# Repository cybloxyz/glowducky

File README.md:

# 🐥 GLOWDUCKY! ver.1 💡
so this glow glow ducky is a bedlamp, not really..it could be another useful things, for study lamp or when lights out or another cute lamp! 
i made this bedlamp for my little sister as gift for her achievement in school! she got first place **🐥** and she likes a little yellow duck! 
*this is my first time working with hardware things!* so i try to make the simplest project, **Lamp ⚡️**.

even in this simplest project i still got so many errors in designing schema..but yeah, trial and error!
i plan to improve this **glowducky** as soon as i learn about Attiny or Atmel, yeaa and i currently learning about Arduino.

wait i'll attach some pics!
## sailor ducky case 🐥

so this duck is going to be the case! you need to separate each body parts so you could put the lamp inside! and i plan to use 3d printer for it with white filament, 2 layers and 0% infill

## pcb and schematic design

this is the glowduck PCB! and i'll attach the schema

### Bill of Materials for each glowducky (BOM)
| Component | Specification | Qty for each lamp | Qty buy | Price | Total Price | 
| :--- | :--- | :--- | :--- | :--- | :--- |
| LED | [5mm Warm White Strawhat ](https://shopee.co.id/LED-Warm-White-5mm-Straw-Hat-Clear-Diode-Super-Bright-Round-Through-i.2178321.42170662136?xptdk=b816d7c5-0220-4b61-b76c-9c2c57219d83) | 2 | 10 | Rp.800 | Rp.8000 |
| Resistor | [330 Ohm](https://shopee.co.id/10X-RESISTOR-330-OHM-1-4W-1-METAL-FILM-i.1078675148.22483412804?xptdk=1b5f20fc-b740-4827-acae-979e2000c763) | 1 | 5 | Rp.700 | Rp.3500 |
| Switch | [8mmx8mm Latching Push Button](https://shopee.co.id/BLUE-CAP-SQUARE-PUSH-BUTTON-8X8MM-SELF-LOCKING-LATCHING-SWITCH-i.1078675148.17199189956?xptdk=031379d1-bf77-44f0-a31d-17c58174d32c) | 1 | 5 | Rp.1033 | Rp.5165 |
| Battery | CR2032 | 2 | 1 strip(5pcs) or 2 strip? | Rp.21500 | Rp.21500 |
| Battery Case | [2x CR2032 Holder](https://shopee.co.id/Baterai-Holder-2X-CR2032-6V-Battery-Case-Tempat-Baterai-Saklar-ON-OFF-i.2178321.24317995442?xptdk=1cde20a7-d5c7-4ba1-88d6-16cacaf16a91) | 1 | 5 | Rp.3600 | Rp.18000 |
| Wire | [AWG 26](https://shopee.co.id/Kabel-AWG-26-awg26-Serabut-Tembaga-Putih-Eceran-1Meter-Jumper-Cable-i.2178321.7345265115?xptdk=d2c1ef28-a399-42a3-8674-fd6ee5da9c35) | 1 (in meter) | 1 | Rp.1800 | Rp.1800 |
| Wire | [Jumper cable male-female](https://shopee.co.id/40PCS-JUMPER-CABLE-KABEL-10CM-MALE-TO-FEMALE-DUPONT-FOR-BREADBOARD-i.1078675148.23482811318?extraParams=%7B%22display_model_id%22%3A89453627299%2C%22model_selection_logic%22%3A2%7D&sp_atk=d1c997f7-9c6e-47e8-9971-6b24501d0b91&xptdk=d1c997f7-9c6e-47e8-9971-6b24501d0b91) | 3 | 1 strip(40pcs) | Rp.9500 | Rp.9500 |
| PCB | [Double layer pcb](https://shopee.co.id/Layanan-Cetak-Pcb-Single-Layer-Dan-Double-Layer-i.100172996.43623177280?xptdk=e2854418-3a2e-4cdc-aff0-7e93d7e86390) | 1 | 5 | Rp.1000 | Rp.5000 |
| Total | Rp.72465 |
| Total + shipping cost | Rp.129465 |

*nb: Price is in IDR, This design is made for minimum quantity (eg: 5 pcs PCB) and some components are not on the pcb (latching button and battery)*

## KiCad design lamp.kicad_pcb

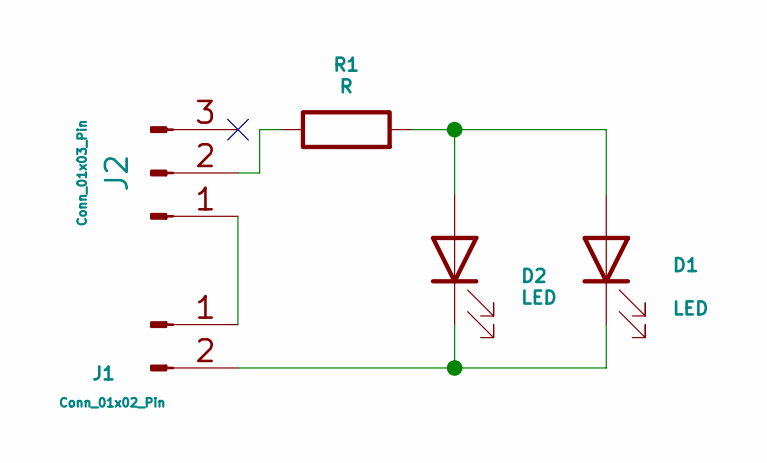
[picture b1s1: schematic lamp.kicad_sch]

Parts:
D1, D2: LED; LED_D5.0mm
J1: Conn_01x02_Pin; PinHeader_1x02_P2.54mm_Vertical
J2: Conn_01x03_Pin; PinHeader_1x03_P2.54mm_Vertical
R1: R; R_Axial_DIN0309_L9.0mm_D3.2mm_P12.70mm_Horizontal

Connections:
unnamed: D1.2 (A), D2.2 (A), R1.2
unnamed: D1.1 (K), D2.1 (K), J1.2
unnamed: J1.1, J2.1
unnamed: J2.2, R1.1

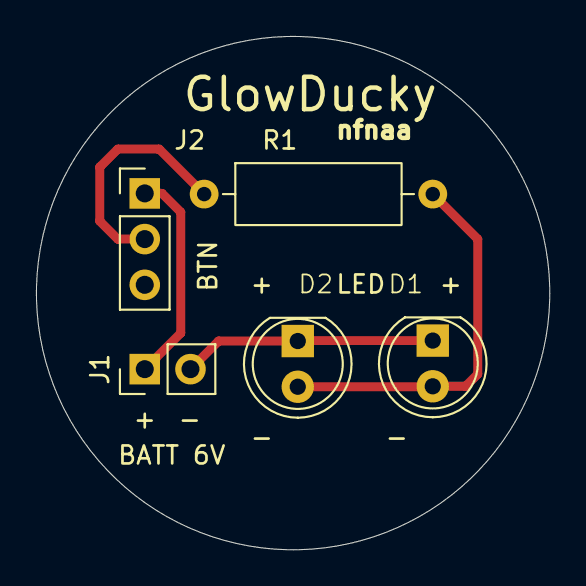
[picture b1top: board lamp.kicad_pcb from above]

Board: 2 copper layers, 28.5 x 28.5 mm, 5 parts (0 on the bottom side), 4 nets.

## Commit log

2025-12-23 done repo
2025-12-23 Fix image links and enhance journal entries
    Updated journal entries with image links and minor text corrections.
2025-12-29 add gerber files and some more
2025-12-29 journalling...
2026-01-08 add kicad project
2026-01-08 Add README for GlowDucky bedlamp project
    Added project details for GlowDucky bedlamp, including descriptions, images, and a Bill of Materials.
2026-01-08 Revise Bill of Materials section in README
    Updated the Bill of Materials section to include specific details for each glowducky and added a note about minimum quantity.
2026-01-08 Update note on PCB design and components
    Clarified note about minimum quantity and missing components.
2026-01-08 Update README with project details and personal story
    Expanded project description and added personal context.
2026-01-08 add 3d case (NONPARTED)
2026-01-22 add link in BOM table
2026-01-22 add specific BOM
2026-01-22 journalling
2026-03-09 re-scaling
2026-03-09 add STEP file
